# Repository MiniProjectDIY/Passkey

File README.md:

# Passkey
use your finterprint to send password via virtual keyboard

# ME
Moduleholder: using screw pillar M2\*4*1.5+2.5\*1, M2\*7 screws

Passkey Case: using 4xM2(screw diameter)\*3(Length)\*3.5(outter diameter) screw inserts,M2\*8 screws

# SW
using project:passkey_tune_and_set to :

1.get module sn

2.register your finterprint

3.change module address(do this at last)

using python project PassKey_utils to encrypt your password with your module sn

using project passkey_final_run to run as final code,

remember to change the module address,the macro define and the encrypted password per your own condition.

# HW
using folder production for PCB/SMT process,or handsolder by yourself.

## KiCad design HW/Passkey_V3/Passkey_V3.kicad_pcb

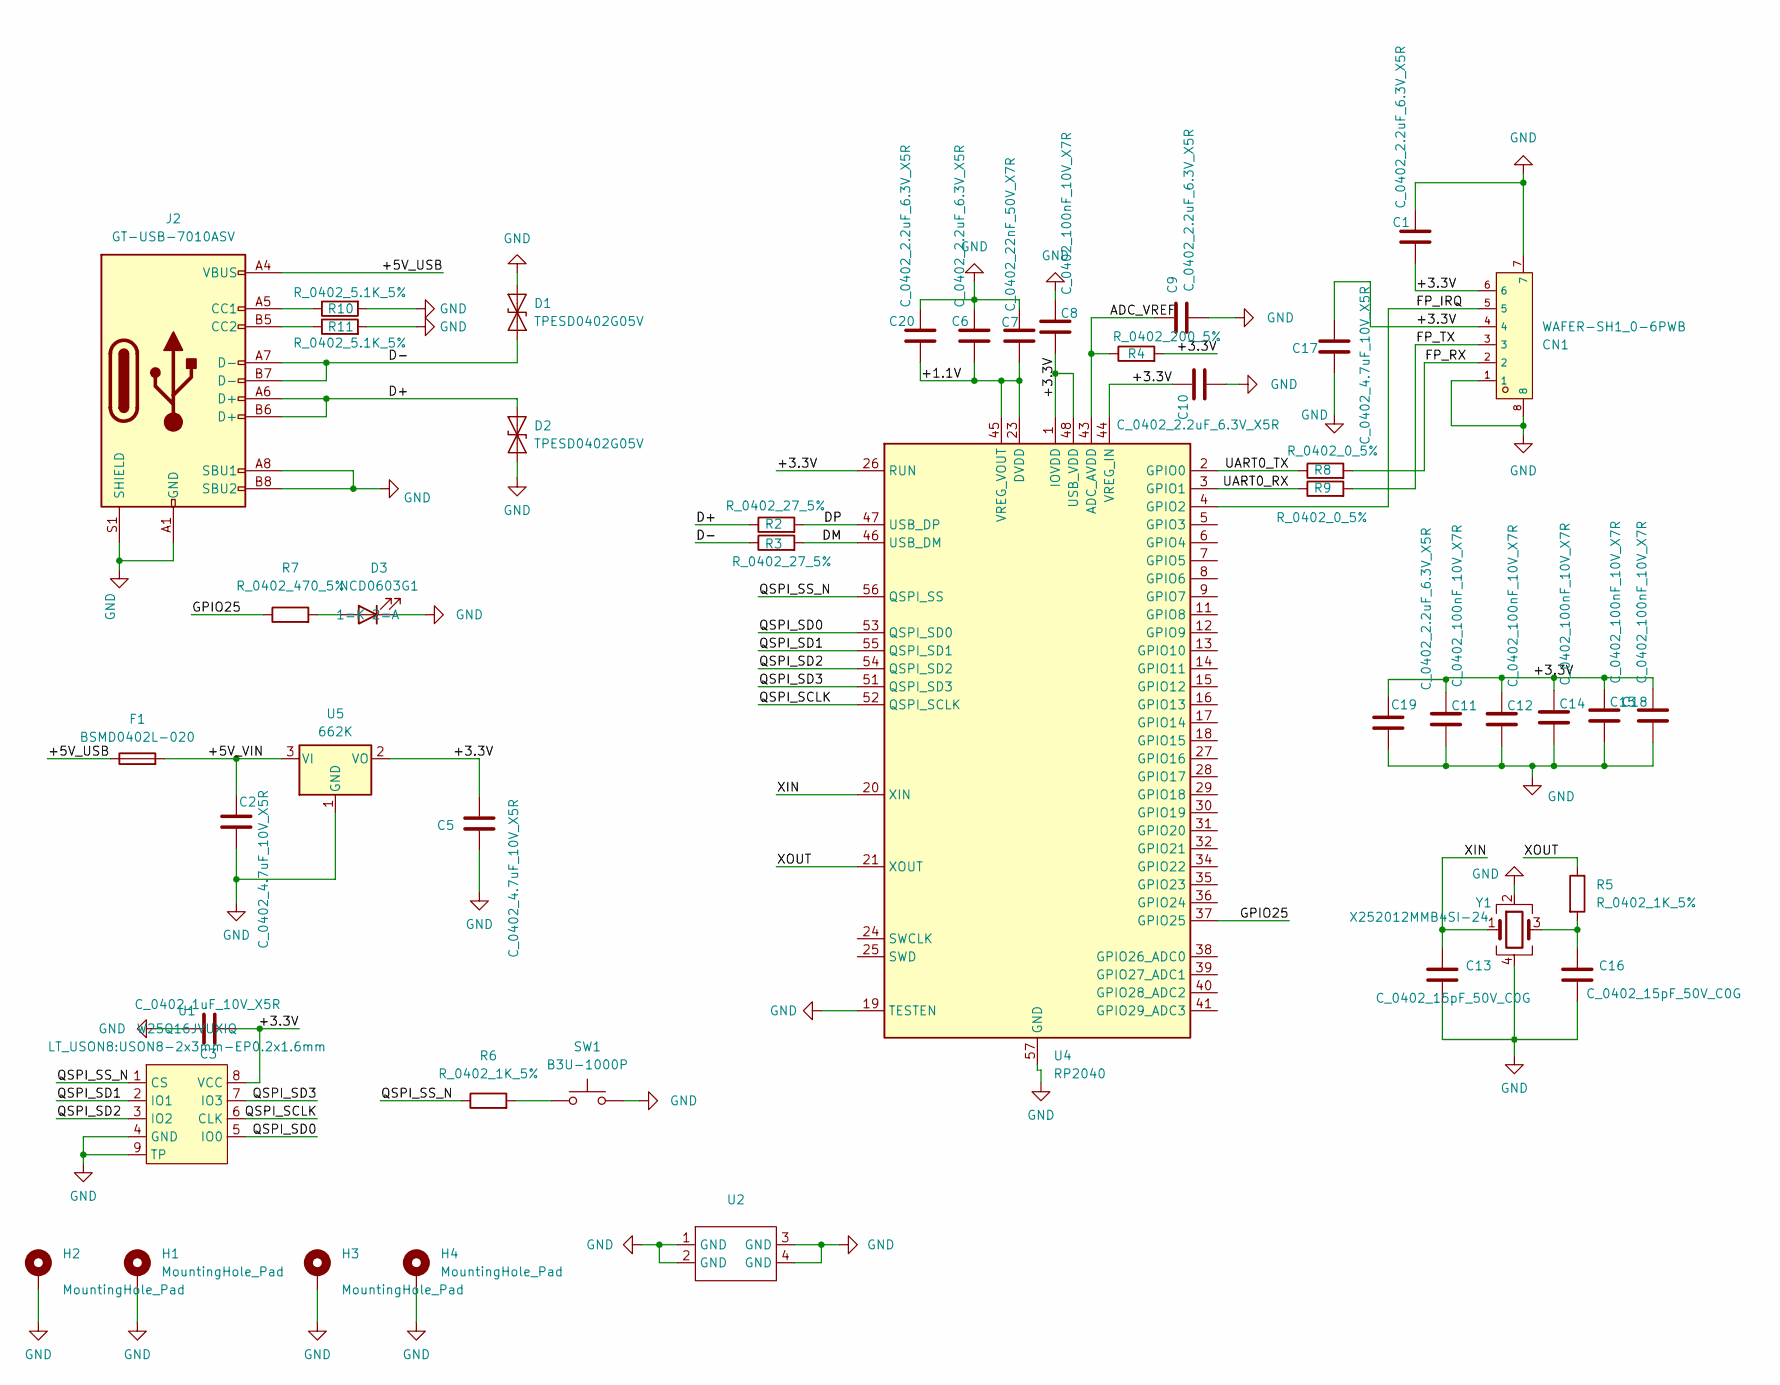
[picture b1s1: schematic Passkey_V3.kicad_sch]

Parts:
C1, C6, C9, C10, C19, C20: C_0402_2.2uF_6.3V_X5R; C_0402_1005Metric
C2, C5, C17: C_0402_4.7uF_10V_X5R; C_0402_1005Metric
C3: C_0402_1uF_10V_X5R; C_0402_1005Metric
C7: C_0402_22nF_50V_X7R; C_0402_1005Metric
C8, C11, C12, C14, C15, C18: C_0402_100nF_10V_X7R; C_0402_1005Metric
C13, C16: C_0402_15pF_50V_C0G; C_0402_1005Metric
CN1: WAFER-SH1_0-6PWB; CONN-SMD_6P-P1.00_XUNPU_WAFER-SH1.0-6PWB; LCSC C3029345
D1, D2: TPESD0402G05V; D0402-BI
D3: NCD0603G1; LED_0603_1608Metric
F1: BSMD0402L-020; Fuse_0402_1005Metric
H1, H2, H3, H4: MountingHole_Pad; MountingHole_2.2mm_M2_Pad
J2: GT-USB-7010ASV; USB_C_Receptacle_G-Switch_GT-USB-7010ASV
R2, R3: R_0402_27_5%; R_0402_1005Metric
R4: R_0402_200_5%; R_0402_1005Metric
R5, R6: R_0402_1K_5%; R_0402_1005Metric
R7: R_0402_470_5%; R_0402_1005Metric
R8, R9: R_0402_0_5%; R_0402_1005Metric
R10, R11: R_0402_5.1K_5%; R_0402_1005Metric
SW1: B3U-1000P; SW_SPST_B3U-1000P
U1: W25Q16JVUXIQ; USON8-2x3mm-EP0.2x1.6mm
U2: ZW101
U4: RP2040; QFN-56-1EP_7x7mm_P0.4mm_EP3.2x3.2mm
U5: 662K; SOT-23
Y1: X252012MMB4SI-24; Crystal_SMD_2520-4Pin_2.5x2.0mm

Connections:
/+1.1V: C6.2, C7.2, C20.2, U4.23 (DVDD), U4.45 (VREG_VOUT), U4.50 (DVDD)
/+3.3V: C1.2, C3.1, C5.1, C8.2, C10.1, C11.1, C12.1, C14.1, C15.1, C17.1, C18.1, C19.2, CN1.4, CN1.6, R4.2, U1.8 (VCC), U4.1 (IOVDD), U4.10 (IOVDD), U4.22 (IOVDD), U4.26 (RUN), U4.33 (IOVDD), U4.42 (IOVDD), U4.44 (VREG_IN), U4.48 (USB_VDD), U4.49 (IOVDD), U5.2 (VO)
/+5V_USB: F1.1, J2.A4 (VBUS), J2.A9 (VBUS), J2.B4 (VBUS), J2.B9 (VBUS)
/+5V_VIN: C2.1, F1.2, U5.3 (VI)
/ADC_VREF: C9.1, R4.1, U4.43 (ADC_AVDD)
/D+: D2.2 (A2), J2.A6 (D+), J2.B6 (D+), R2.1
/D-: D1.1 (A1), J2.A7 (D-), J2.B7 (D-), R3.1
/DM: R3.2, U4.46 (USB_DM)
/DP: R2.2, U4.47 (USB_DP)
/FP_IRQ: CN1.5, U4.4 (GPIO2)
/FP_RX: CN1.2, R8.2
/FP_TX: CN1.3, R9.2
/GPIO25: R7.1, U4.37 (GPIO25)
/QSPI_SCLK: U1.6 (CLK), U4.52 (QSPI_SCLK)
/QSPI_SD0: U1.5 (IO0), U4.53 (QSPI_SD0)
/QSPI_SD1: U1.2 (IO1), U4.55 (QSPI_SD1)
/QSPI_SD2: U1.3 (IO2), U4.54 (QSPI_SD2)
/QSPI_SD3: U1.7 (IO3), U4.51 (QSPI_SD3)
/QSPI_SS_N: R6.1, U1.1 (CS), U4.56 (QSPI_SS)
/UART0_RX: R9.1, U4.3 (GPIO1)
/UART0_TX: R8.1, U4.2 (GPIO0)
/XIN: C13.1, U4.20 (XIN), Y1.1
/XOUT: R5.1, U4.21 (XOUT)
GND: C1.1, C2.2, C3.2, C5.2, C6.1, C7.1, C8.1, C9.2, C10.2, C11.2, C12.2, C13.2, C14.2, C15.2, C16.2, C17.2, C18.2, C19.1, C20.1, CN1.1, CN1.7, CN1.8, D1.2 (A2), D2.1 (A1), D3.1 (K), H1.1, H2.1, H3.1, H4.1, J2.A1 (GND), J2.A8 (SBU1), J2.A12 (GND), J2.B1 (GND), J2.B8 (SBU2), J2.B12 (GND), J2.S1 (SHIELD), R10.2, R11.2, SW1.2, U1.4 (GND), U1.9 (TP), U2.1 (GND), U2.2 (GND), U2.3 (GND), U2.4 (GND), U4.19 (TESTEN), U4.57 (GND), U5.1 (GND), Y1.2, Y1.4
unnamed: C16.1, R5.2, Y1.3
unnamed: D3.2 (A), R7.2
unnamed: J2.A5 (CC1), R10.1
unnamed: J2.B5 (CC2), R11.1
unnamed: R6.2, SW1.1

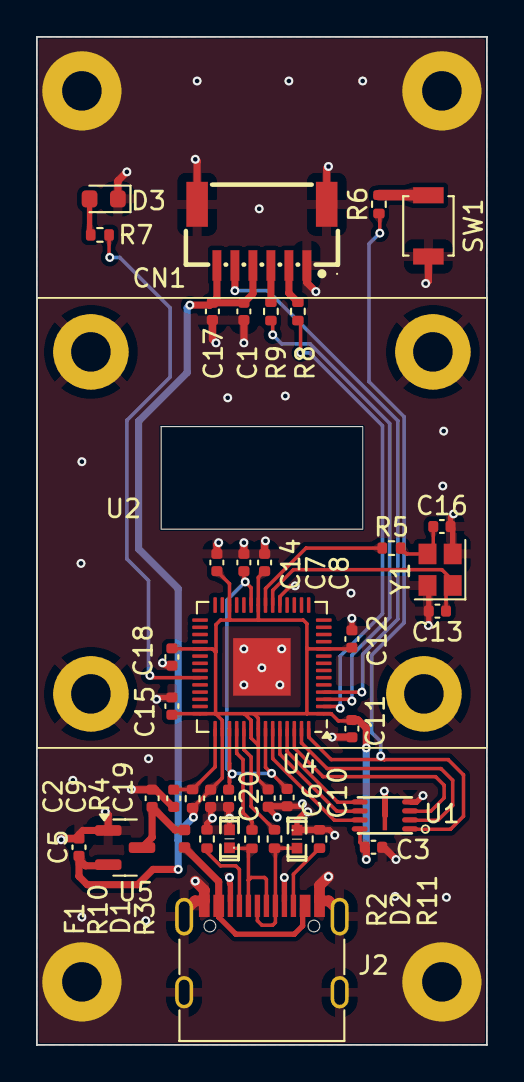
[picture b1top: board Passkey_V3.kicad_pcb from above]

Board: 2 copper layers, 25.0 x 56.0 mm, 45 parts (0 on the bottom side), 29 nets.

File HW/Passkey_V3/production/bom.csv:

Designator,Footprint,Quantity,Value,LCSC Part #
"C1, C10, C19, C20, C6, C9",0402,6,C_0402_2.2uF_6.3V_X5R,
"C11, C12, C14, C15, C18, C8",0402,6,C_0402_100nF_10V_X7R,
"C13, C16",0402,2,C_0402_15pF_50V_C0G,
"C17, C2, C5",0402,3,C_0402_4.7uF_10V_X5R,
C3,0402,1,C_0402_1uF_10V_X5R,
C7,0402,1,C_0402_22nF_50V_X7R,
CN1,CONN-SMD_6P-P1.00_XUNPU_WAFER-SH1.0-6PWB,1,WAFER-SH1_0-6PWB,C3029345
"D1, D2",0402,2,TPESD0402G05V,
D3,0603,1,NCD0603G1,
F1,0402,1,BSMD0402L-020,
J2,USB_C_Receptacle_G-Switch_GT-USB-7010ASV,1,GT-USB-7010ASV,
"R10, R11",0402,2,R_0402_5.1K_5%,
"R2, R3",0402,2,R_0402_27_5%,
R4,0402,1,R_0402_200_5%,
"R5, R6",0402,2,R_0402_1K_5%,
R7,0402,1,R_0402_470_5%,
"R8, R9",0402,2,R_0402_0_5%,
SW1,SW_SPST_B3U-1000P,1,B3U-1000P,
U1,USON8-2x3mm-EP0.2x1.6mm,1,W25Q16JVUXIQ,
U2,ZW101,1,~,
U4,QFN-56-1EP_7x7mm_P0.4mm_EP3.2x3.2mm,1,RP2040,
U5,SOT-23,1,662K,
Y1,Crystal_SMD_2520-4Pin_2.5x2.0mm,1,X252012MMB4SI-24,

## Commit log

2025-08-31 Initial
